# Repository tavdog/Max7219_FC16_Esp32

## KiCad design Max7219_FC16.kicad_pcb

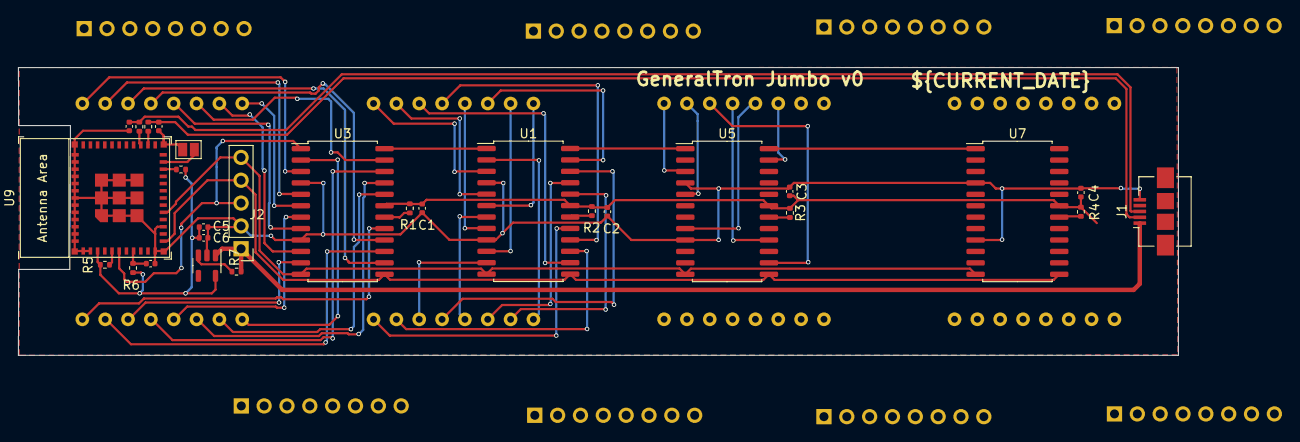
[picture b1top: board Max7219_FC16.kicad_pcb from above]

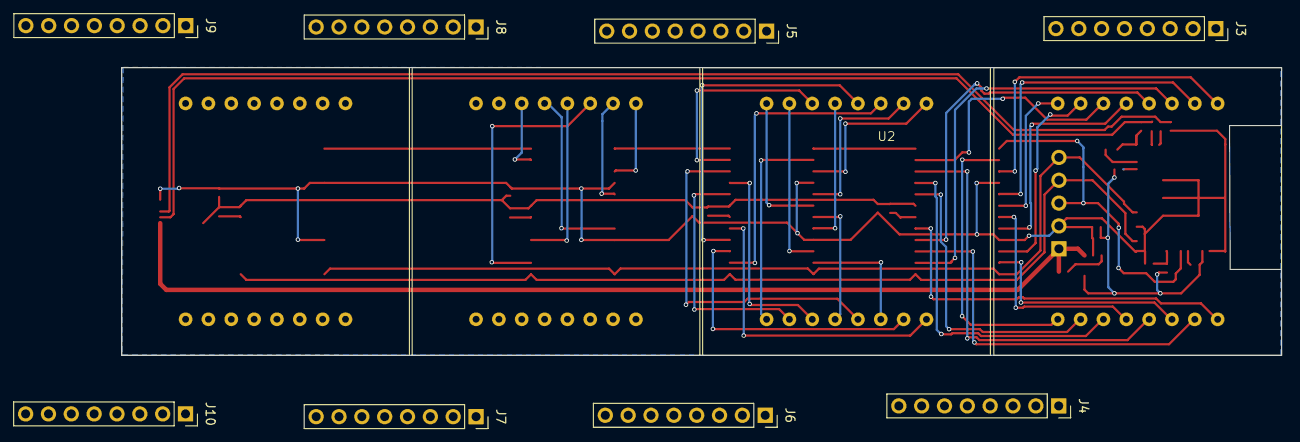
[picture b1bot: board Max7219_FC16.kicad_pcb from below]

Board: 2 copper layers, 129.0 x 32.0 mm, 40 parts (12 on the bottom side), 86 nets.

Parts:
C1, C2, C3, C4, C5, C7, C8, C9: 0.1uF; C_0402_1005Metric
C6: 10uF; C_0402_1005Metric
J1: USB_B_Micro; USB_Micro-B_Amphenol_10104110_Horizontal
J2: Conn_01x05_Pin; PinHeader_1x05_P2.54mm_Vertical
J3, J4, J5, J6, J7, J8, J9, J10: Conn_01x08_Socket; PinSocket_1x08_P2.54mm_Vertical
JP1: Boot; SolderJumper-2_P1.3mm_Open_Pad1.0x1.5mm
R1, R2, R3, R4, R5, R6, R10: 10k; R_0402_1005Metric
R7: 1k; R_0402_1005Metric
R8, R9: 0; R_0402_1005Metric
U1, U3, U5, U7: MAX7221xWG; SOIC-24W_7.5x15.4mm_P1.27mm
U2, U4, U6, U8: KWM-30881CVB; 8x8
U9: ESP32-C3-MINI-1
U10: AP2112K-3.3; SOT-23-5

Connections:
+3.3V: C5.2, C6.2, R5.1, R6.1, R10.1, U9.3 (3V3), U10.5 (VOUT)
/ESP32 Section/CLK: J2.4, U1.13 (CLK), U3.13 (CLK), U5.13 (CLK), U7.13 (CLK), U9.12 (GPIO0/ADC1_CH0/XTAL_32K_P)
/ESP32 Section/CS: J2.5, U1.12 (~CS), U3.12 (~CS), U5.12 (~CS), U7.12 (~CS), U9.16 (GPIO10)
/ESP32 Section/MOSI: J2.3, U3.1 (DIN), U9.6 (GPIO3/ADC1_CH3)
/Max7219_8x8/DOUT: U1.1 (DIN), U3.24 (DOUT)
/Max7219_8x10/DIN: U1.24 (DOUT), U5.1 (DIN)
/Max7219_8x10/DOUT: U5.24 (DOUT), U7.1 (DIN)
GND: C1.2, C2.2, C3.2, C4.2, C5.1, C6.1, C7.2, C8.2, C9.2, J1.5 (GND), J1.6 (Shield), J2.2, JP1.2 (B), U1.4 (GND), U1.9 (GND), U3.4 (GND), U3.9 (GND), U5.4 (GND), U5.9 (GND), U7.4 (GND), U7.9 (GND), U9.1 (GND), U9.2 (GND), U9.11 (GND), U9.14 (GND), U9.36 (GND), U9.37 (GND), U9.38 (GND), U9.39 (GND), U9.40 (GND), U9.41 (GND), U9.42 (GND), U9.43 (GND), U9.44 (GND), U9.45 (GND), U9.46 (GND), U9.47 (GND), U9.48 (GND), U9.49 (GND), U9.50 (GND), U9.51 (GND), U9.52 (GND), U9.53 (GND), U10.2 (GND)
unnamed: C8.1, J1.3 (D+), R9.2
unnamed: C7.1, J1.2 (D-), R8.2
unnamed: JP1.1 (A), U9.23 (GPIO9)
unnamed: U1.2 (DIG_0), U2.9 (R1)
unnamed: U1.11 (DIG_1), U2.14 (R2)
unnamed: U1.6 (DIG_2), U2.8 (R3)
unnamed: U1.7 (DIG_3), U2.12 (R4)
unnamed: U1.3 (DIG_4), U2.1 (R5)
unnamed: U1.10 (DIG_5), U2.7 (R6)
unnamed: U1.5 (DIG_6), U2.2 (R7)
unnamed: U1.8 (DIG_7), U2.5 (R8)
unnamed: R2.2, U1.18 (ISET)
unnamed: U1.14 (SEG_A), U2.3 (C2)
unnamed: U1.16 (SEG_B), U2.4 (C3)
unnamed: U1.20 (SEG_C), U2.10 (C4)
unnamed: U1.23 (SEG_D), U2.6 (C5)
unnamed: U1.22 (SEG_DP), U2.13 (C1)
unnamed: U1.21 (SEG_E), U2.11 (C6)
unnamed: U1.15 (SEG_F), U2.15 (C7)
unnamed: U1.17 (SEG_G), U2.16 (C8)
unnamed: U3.2 (DIG_0), U4.9 (R1)
unnamed: U3.11 (DIG_1), U4.14 (R2)
unnamed: U3.6 (DIG_2), U4.8 (R3)
unnamed: U3.7 (DIG_3), U4.12 (R4)
unnamed: U3.3 (DIG_4), U4.1 (R5)
unnamed: U3.10 (DIG_5), U4.7 (R6)
unnamed: U3.5 (DIG_6), U4.2 (R7)
unnamed: U3.8 (DIG_7), U4.5 (R8)
unnamed: R1.2, U3.18 (ISET)
unnamed: U3.14 (SEG_A), U4.3 (C2)
unnamed: U3.16 (SEG_B), U4.4 (C3)
unnamed: U3.20 (SEG_C), U4.10 (C4)
unnamed: U3.23 (SEG_D), U4.6 (C5)
unnamed: U3.22 (SEG_DP), U4.13 (C1)
unnamed: U3.21 (SEG_E), U4.11 (C6)
unnamed: U3.15 (SEG_F), U4.15 (C7)
unnamed: U3.17 (SEG_G), U4.16 (C8)
unnamed: U5.2 (DIG_0), U6.9 (R1)
unnamed: U5.11 (DIG_1), U6.14 (R2)
unnamed: U5.6 (DIG_2), U6.8 (R3)
unnamed: U5.7 (DIG_3), U6.12 (R4)
unnamed: U5.3 (DIG_4), U6.1 (R5)
unnamed: U5.10 (DIG_5), U6.7 (R6)
unnamed: U5.5 (DIG_6), U6.2 (R7)
unnamed: U5.8 (DIG_7), U6.5 (R8)
unnamed: R3.2, U5.18 (ISET)
unnamed: U5.14 (SEG_A), U6.3 (C2)
unnamed: U5.16 (SEG_B), U6.4 (C3)
unnamed: U5.20 (SEG_C), U6.10 (C4)
unnamed: U5.23 (SEG_D), U6.6 (C5)
unnamed: U5.22 (SEG_DP), U6.13 (C1)
unnamed: U5.21 (SEG_E), U6.11 (C6)
unnamed: U5.15 (SEG_F), U6.15 (C7)
unnamed: U5.17 (SEG_G), U6.16 (C8)
unnamed: U7.2 (DIG_0), U8.9 (R1)
unnamed: U7.11 (DIG_1), U8.14 (R2)
unnamed: U7.6 (DIG_2), U8.8 (R3)
unnamed: U7.7 (DIG_3), U8.12 (R4)
unnamed: U7.3 (DIG_4), U8.1 (R5)
unnamed: U7.10 (DIG_5), U8.7 (R6)
unnamed: U7.5 (DIG_6), U8.2 (R7)
unnamed: U7.8 (DIG_7), U8.5 (R8)
unnamed: R4.2, U7.18 (ISET)
unnamed: U7.14 (SEG_A), U8.3 (C2)
unnamed: U7.16 (SEG_B), U8.4 (C3)
unnamed: U7.20 (SEG_C), U8.10 (C4)
unnamed: U7.23 (SEG_D), U8.6 (C5)
unnamed: U7.22 (SEG_DP), U8.13 (C1)
unnamed: U7.21 (SEG_E), U8.11 (C6)
unnamed: U7.15 (SEG_F), U8.15 (C7)
unnamed: U7.17 (SEG_G), U8.16 (C8)
unnamed: C9.1, R6.2, U9.8 (EN/CHIP_PU)
unnamed: R5.2, U9.5 (GPIO2/ADC1_CH2)
unnamed: R10.2, U9.22 (GPIO8)
unnamed: R8.1, U9.26 (GPIO18/USB_D-)
unnamed: R9.1, U9.27 (GPIO19/USB_D+)
unnamed: R7.2, U10.3 (EN)
VUSB: C1.1, C2.1, C3.1, C4.1, J1.1 (VBUS), J2.1, R1.1, R2.1, R3.1, R4.1, R7.1, U1.19 (V+), U3.19 (V+), U5.19 (V+), U7.19 (V+), U10.1 (VIN)

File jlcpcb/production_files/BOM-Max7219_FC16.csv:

Comment,Designator,Footprint,LCSC
10k,R10,R_0402_1005Metric,
Jumper_2_Open,JP1,SolderJumper-2_P1.3mm_Open_Pad1.0x1.5mm,
Conn_01x05_Pin,J2,PinHeader_1x05_P2.54mm_Vertical,
0,R9,R_0402_1005Metric,
0,R8,R_0402_1005Metric,
USB_B_Micro,J1,USB_Micro-B_Amphenol_10118194_Horizontal,
0.1,C8,C_0402_1005Metric,
0.1,C7,C_0402_1005Metric,
0.1uF,C3,C_0402_1005Metric,
10k,R3,R_0402_1005Metric,
MAX7221xWG,U5,SOIC-24W_7.5x15.4mm_P1.27mm,
AP2112K-3.3,U10,SOT-23-5,
MAX7221xWG,U1,SOIC-24W_7.5x15.4mm_P1.27mm,
1k,R7,R_0402_1005Metric,
1k,R6,R_0402_1005Metric,
10k,R5,R_0402_1005Metric,
10k,R2,R_0402_1005Metric,
10k,R1,R_0402_1005Metric,
10,C6,C_0402_1005Metric,
0.1,C5,C_0402_1005Metric,
0.1uF,C2,C_0402_1005Metric,
0.1uF,C1,C_0402_1005Metric,
0.1uF,C4,C_0402_1005Metric,
10k,R4,R_0402_1005Metric,
MAX7221xWG,U3,SOIC-24W_7.5x15.4mm_P1.27mm,
MAX7221xWG,U7,SOIC-24W_7.5x15.4mm_P1.27mm,
C3Mini,U9,ESP32-C3-MINI-1,

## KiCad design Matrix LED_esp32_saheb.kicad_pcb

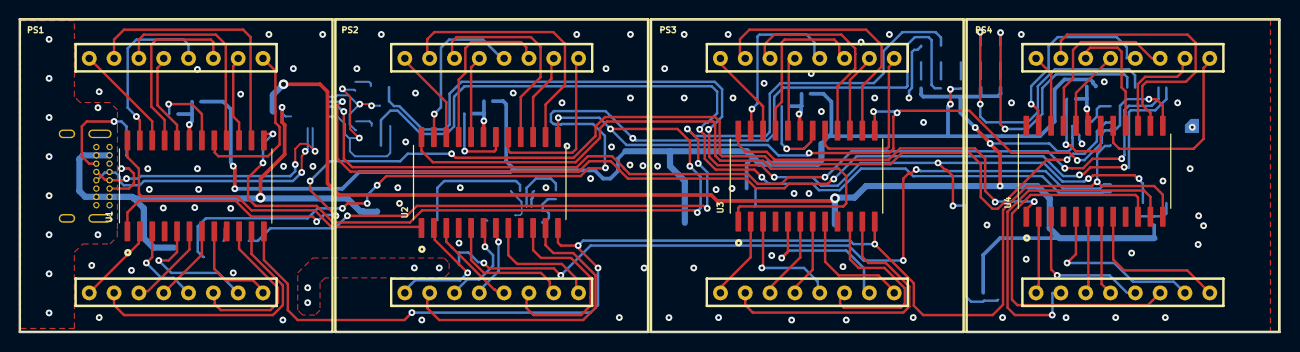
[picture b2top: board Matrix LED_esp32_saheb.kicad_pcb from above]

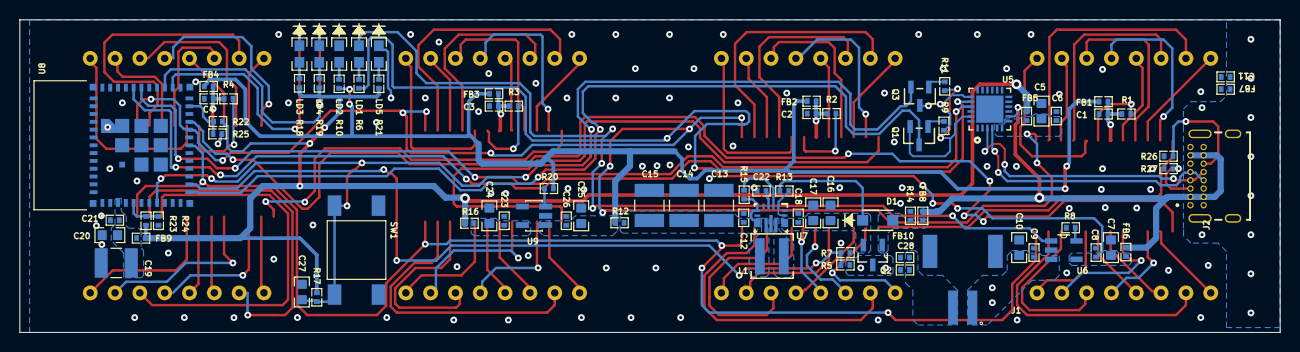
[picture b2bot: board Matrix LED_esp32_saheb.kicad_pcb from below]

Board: 2 copper layers, 129.0 x 32.0 mm, 91 parts (83 on the bottom side), 122 nets.

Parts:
C1, C2, C3, C4, C6, C8, C9, C11, C12, C18, C21, C22, C23, C26, C28: 0.1uF/50V; CAP_0402
C5, C7, C10, C16, C17, C20, C24, C25, C27: 10uF/10V; CAP_0603
C13, C14, C15, C19: 22uF/16V; TANT_22uF
D1: MBR120LSFT3G
FB1, FB2, FB3, FB4, FB5, FB6, FB7, FB8, FB9, FB10: 120E; RES_0402
J1: S2B-PH-SM4-TB; JST_S2B-PH-SM4-TB
J2: USB4085-GF-A; GCT_USB4085-GF-A_REVB
L1: CMLW4030S1R5NST; IND_4X4
LD1, LD2, LD4, LD5: GREEN/2V; LED_0603
LD3: RED/2V; LED_0603
PS1, PS2, PS3, PS4: LED Matrix_8X8; LED Matrix 8X8_New
Q1, Q3: FMMT491TA
Q2: DMG3415U-7
R1, R2, R3, R4, R9, R10, R11, R13, R17, R18, R19, R21: 10K; RES_0402
R5, R7, R14, R15, R20: 100K; RES_0402
R6: 3.3K; RES_0402
R8: 4.7K; RES_0402
R12, R16, R22, R23, R24, R25: 0E; RES_0402
R26, R27: 5.1K; RES_0402
SW1: TL3301NF160QG-KR; SW_TL3301NF160QG
U1, U2, U3, U4: MAX7219CWG+T
U5: CP2104-F03-GMR
U6: MCP73831T-2ACI/OT
U7: TPS630701RNMR; RNM0015A
U8: ESP32-C3-MINI-1-N4; XCVR_ESP32-C3-MINI-1-N4
U9: AP2112K-3.3TRG1

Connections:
ADC_BAT: R5.1, R7.2, U8.13
DRV1_OUT: U1.24, U2.1
DRV2_OUT: U2.24, U3.1
DRV3_OUT: U3.24, U4.1
DRV_CLK: U1.13, U2.13, U3.13, U4.13, U8.20
DRV_CS: U1.12, U2.12, U3.12, U4.12, U8.18
DRV_IN: U1.1, U8.21
DTR: Q1.2, R11.1, U5.23
EN: C27.2, Q3.2, R17.1, SW1.3, SW1.4, U8.8
ESP32_RX: U5.21, U8.30
ESP32_TX: U5.20, U8.31
GND: C1.1, C2.1, C3.1, C4.1, C5.1, C6.1, C7.1, C8.1, C9.1, C10.1, C11.1, C12.1, C13.1, C14.1, C15.1, C16.1, C17.1, C18.1, C19.1, C20.1, C21.1, C22.1, C23.1, C24.1, C25.1, C26.1, C27.1, C28.1, FB7.1, FB10.1, J1.P1, J1.P2, LD2.1, LD5.1, R7.1, R8.1, R14.1, R24.1, R25.1, R26.1, R27.1, SW1.1, SW1.2, U1.4, U1.9, U2.4, U2.9, U3.4, U3.9, U4.4, U4.9, U5.2, U5.25, U6.2, U7.4, U7.6, U7.10, U7.15, U8.1, U8.2, U8.11, U8.14, U8.36, U8.37, U8.38, U8.39, U8.40, U8.41, U8.42, U8.43, U8.44, U8.45, U8.46, U8.47, U8.48, U8.49_1, U8.49_2, U8.49_3, U8.49_4, U8.49_5, U8.49_6, U8.49_7, U8.49_8, U8.49_9, U8.50, U8.51, U8.52, U8.53, U9.2
GREEN: LD4.1, U8.27
IO0: Q1.3, U8.12
NetC1_2: C1.2, FB1.2, R1.1, U1.19
NetC2_2: C2.2, FB2.2, R2.1, U2.19
NetC3_2: C3.2, FB3.2, R3.1, U3.19
NetC4_2: C4.2, FB4.2, R4.1, U4.19
NetC5_2: C5.2, C6.2, FB5.1, U5.5, U5.6, U5.7
NetC7_2: C7.2, C8.2, FB6.2, R6.1, U6.4
NetC11_2: C11.2, FB7.2, J2.A1, J2.A12, J2.B1, J2.B12, J2.S1, J2.S2, J2.S3, J2.S4
NetC12_2: C12.2, C13.2, C14.2, C15.2, R12.1, R15.1, U7.5, U7.7, U7.8
NetC16_2: C16.2, C17.2, C18.2, D1.1, Q2.2, R13.1, U7.12, U7.13
NetC19_2: C19.2, C20.2, C21.2, FB9.2, U8.3
NetC22_2: C22.2, U7.3
NetC23_2: C23.2, C24.2, R16.1, U9.5
NetD1_2: D1.2, FB8.2, Q2.1, R14.2
NetJ2_A5: J2.A5, R27.2
NetJ2_A6: J2.A6, J2.B6, U5.3
NetJ2_A7: J2.A7, J2.B7, U5.4
NetJ2_B5: J2.B5, R26.2
NetL1_1: L1.1, U7.9
NetL1_2: L1.2, U7.11
NetLD1_2: LD1.2, R6.2
NetLD2_2: LD2.2, R10.2
NetLD3_2: LD3.2, R18.1
NetLD4_2: LD4.2, R19.1
NetLD5_2: LD5.2, R21.2
NetPS1_1: PS1.1, U1.2
NetPS1_2: PS1.2, U1.11
NetPS1_3: PS1.3, U1.6
NetPS1_4: PS1.4, U1.7
NetPS1_5: PS1.5, U1.3
NetPS1_6: PS1.6, U1.10
NetPS1_7: PS1.7, U1.5
NetPS1_8: PS1.8, U1.8
NetPS1_9: PS1.9, U1.17
NetPS1_10: PS1.10, U1.15
NetPS1_11: PS1.11, U1.21
NetPS1_12: PS1.12, U1.23
NetPS1_13: PS1.13, U1.20
NetPS1_14: PS1.14, U1.16
NetPS1_15: PS1.15, U1.14
NetPS1_16: PS1.16, U1.22
NetPS2_1: PS2.1, U2.2
NetPS2_2: PS2.2, U2.11
NetPS2_3: PS2.3, U2.6
NetPS2_4: PS2.4, U2.7
NetPS2_5: PS2.5, U2.3
NetPS2_6: PS2.6, U2.10
NetPS2_7: PS2.7, U2.5
NetPS2_8: PS2.8, U2.8
NetPS2_9: PS2.9, U2.17
NetPS2_10: PS2.10, U2.15
NetPS2_11: PS2.11, U2.21
NetPS2_12: PS2.12, U2.23
NetPS2_13: PS2.13, U2.20
NetPS2_14: PS2.14, U2.16
NetPS2_15: PS2.15, U2.14
NetPS2_16: PS2.16, U2.22
NetPS3_1: PS3.1, U3.2
NetPS3_2: PS3.2, U3.11
NetPS3_3: PS3.3, U3.6
NetPS3_4: PS3.4, U3.7
NetPS3_5: PS3.5, U3.3
NetPS3_6: PS3.6, U3.10
NetPS3_7: PS3.7, U3.5
NetPS3_8: PS3.8, U3.8
NetPS3_9: PS3.9, U3.17
NetPS3_10: PS3.10, U3.15
NetPS3_11: PS3.11, U3.21
NetPS3_12: PS3.12, U3.23
NetPS3_13: PS3.13, U3.20
NetPS3_14: PS3.14, U3.16
NetPS3_15: PS3.15, U3.14
NetPS3_16: PS3.16, U3.22
NetPS4_1: PS4.1, U4.2
NetPS4_2: PS4.2, U4.11
NetPS4_3: PS4.3, U4.6
NetPS4_4: PS4.4, U4.7
NetPS4_5: PS4.5, U4.3
NetPS4_6: PS4.6, U4.10
NetPS4_7: PS4.7, U4.5
NetPS4_8: PS4.8, U4.8
NetPS4_9: PS4.9, U4.17
NetPS4_10: PS4.10, U4.15
NetPS4_11: PS4.11, U4.21
NetPS4_12: PS4.12, U4.23
NetPS4_13: PS4.13, U4.20
NetPS4_14: PS4.14, U4.16
NetPS4_15: PS4.15, U4.14
NetPS4_16: PS4.16, U4.22
NetQ1_1: Q1.1, R9.2
NetQ3_1: Q3.1, R11.2
NetR1_2: R1.2, U1.18
NetR2_2: R2.2, U2.18
NetR3_2: R3.2, U3.18
NetR4_2: R4.2, U4.18
NetR8_2: R8.2, U6.5
NetR13_2: R13.2, U7.1, U7.14
NetR15_2: R15.2, U7.2
NetR20_1: R20.1, U9.3
NetR22_1: R22.1, R25.2, U8.23
NetR23_1: R23.1, R24.2, U8.5
RED: LD3.1, U8.26
RTS: Q3.3, R9.1, U5.19
STAT: LD1.1, U6.1
VBAT+: C9.2, C10.2, J1.1, Q2.3, R5.2, U6.3
VBAT-: C28.2, FB10.2, J1.2
VBUS: FB6.1, FB8.1, J2.A4, J2.A9, J2.B4, J2.B9, U5.8
VCC_3V3: FB5.2, FB9.1, R16.2, R17.2, R18.2, R19.2, R21.1, R22.2, R23.2
VCC_5V: C25.2, C26.2, FB1.1, FB2.1, FB3.1, FB4.1, R10.1, R12.2, R20.2, U9.1

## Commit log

2024-01-24 so many changes.
2024-01-25 almost to jlpcb
2024-01-26 machine pin headers
2024-01-26 cleanout old files
2024-01-28 latest change
2024-01-29 first max routed
